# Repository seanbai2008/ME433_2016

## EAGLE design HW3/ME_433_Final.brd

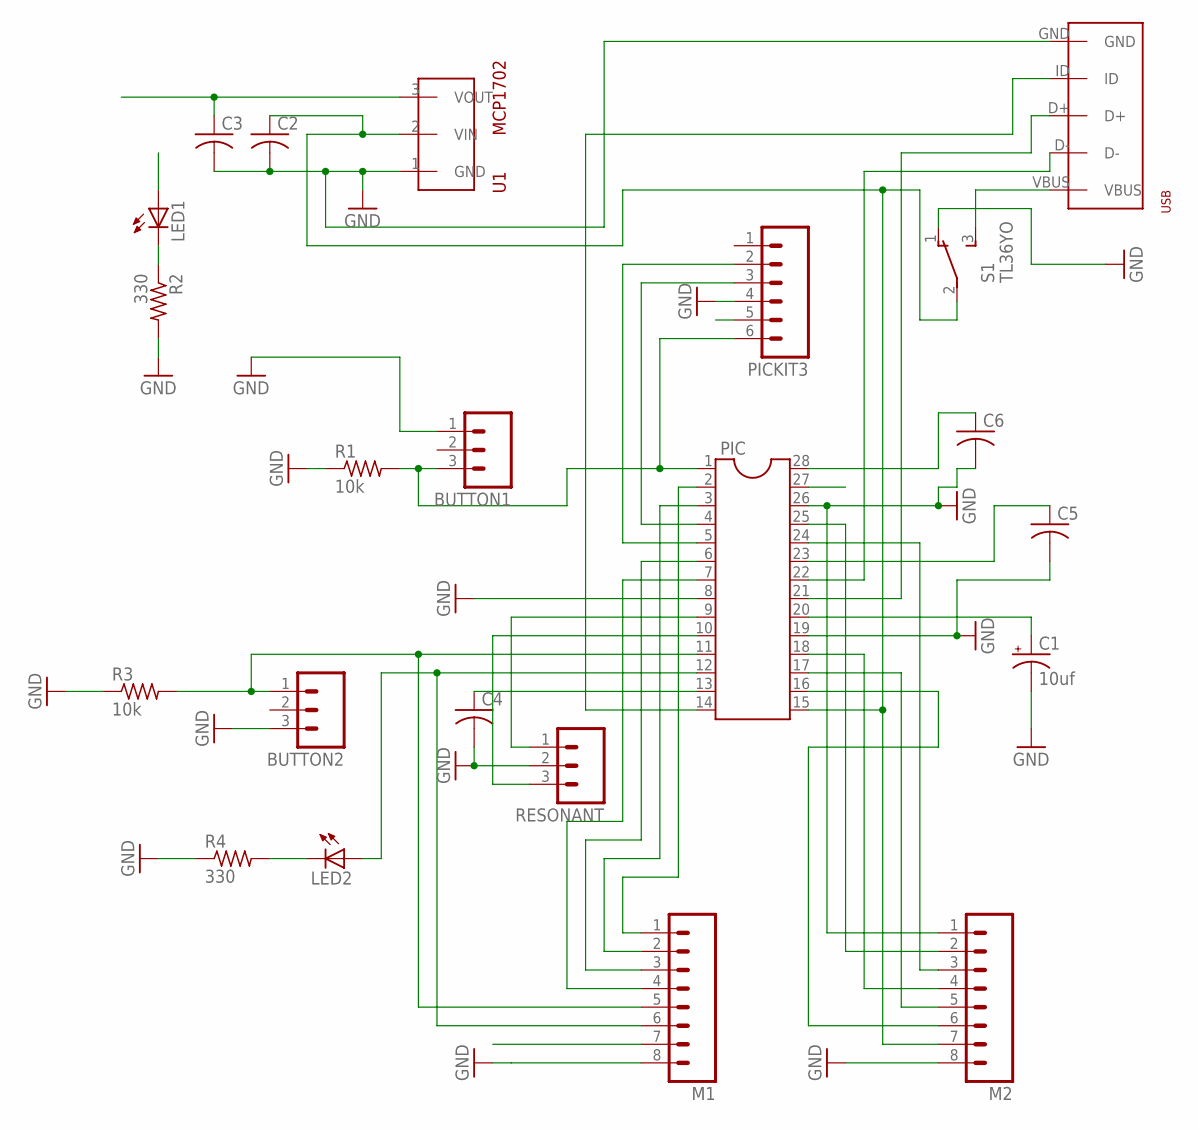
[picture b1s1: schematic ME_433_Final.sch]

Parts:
BUTTON1, BUTTON2: M03PTH; 1X03
C1: 10uf; E5-10,5
C2, C3, C4, C5, C6: C-US025-025X050; C025-025X050
LED1, LED2: LED3MM
M1, M2: M08SILK_FEMALE_PTH; 1X08
PIC: DIL28-3
PICKIT3: M06SILK_FEMALE_PTH; 1X06
R1, R3: 10k; 0309/12
R2, R4: 330; 0309/12
RESONANT: M03PTH; 1X03
S1: TL36YO; TL3XYO
U$1: MCP1702TO92; TO92
U$2: USB_ME; USB-MB-H

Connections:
3.3V: C3.1, C4.1, C5.1, C6.1, LED1.A, M1.7, PIC.13, PIC.23, PIC.28, PICKIT3.5, U$1.3 (VOUT)
GND: BUTTON1.1, BUTTON2.3, C1.-, C2.2, C3.2, C4.2, C5.2, C6.2, M1.8, M2.1, M2.8, PIC.8, PIC.19, PIC.26, PICKIT3.4, R1.1, R2.2, R3.1, R4.1, RESONANT.2, S1.1 (O), U$1.1 (GND), U$2.GND
unnamed: BUTTON1.3, PIC.1, PICKIT3.6, R1.2
unnamed: PIC.4, PICKIT3.3
unnamed: C2.1, M2.7, PIC.15, S1.2, U$1.2 (VIN)
unnamed: LED1.K (C), R2.1
unnamed: PIC.5, PICKIT3.2
unnamed: PIC.9, RESONANT.1
unnamed: PIC.10, RESONANT.3
unnamed: BUTTON2.1, M1.5, PIC.11, R3.2
unnamed: PIC.14, U$2.ID
unnamed: LED2.A, M1.6, PIC.12
unnamed: LED2.K (C), R4.2
unnamed: C1.+, PIC.20
unnamed: PIC.21, U$2.D+
unnamed: PIC.22, U$2.D-
unnamed: M1.1, PIC.2
unnamed: M1.2, PIC.3
unnamed: M1.3, PIC.6
unnamed: M1.4, PIC.7
unnamed: M2.2, PIC.25
unnamed: M2.3, PIC.24
unnamed: M2.4, PIC.18
unnamed: M2.5, PIC.17
unnamed: M2.6, PIC.16
unnamed: S1.3 (S), U$2.VBUS

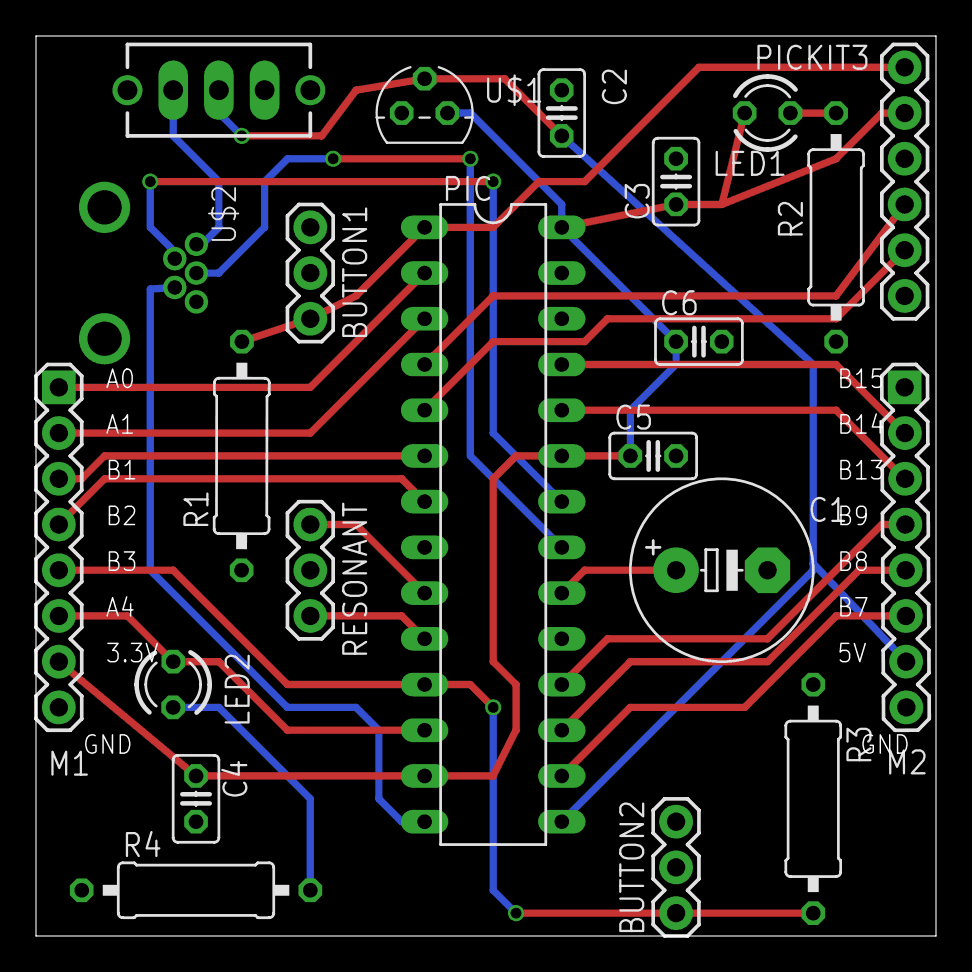
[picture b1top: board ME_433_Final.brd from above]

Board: 2 copper layers, 50.0 x 50.0 mm, 22 parts (0 on the bottom side), 26 nets.

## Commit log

2016-04-05 modify the README for HW1
2016-04-14 Ready to get checked before order
2016-05-19 add more homeworks
2016-06-04 add figure for HW4
2016-06-04 ad figures
2016-06-04 change readme
2016-06-04 add readme
2016-06-05 add hw8
2016-06-05 add hw10
2016-06-05 add hw12 and hw13
2016-06-08 add contents
2016-06-08 modify
2016-06-08 add HW13
2016-06-08 add HW16
2016-06-08 add hw9
